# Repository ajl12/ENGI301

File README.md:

# Stress Buddy

The following repository contains files required to operate the Stress Buddy device created using a PocketBeagle.

For more information on how to build the device and connect hardware, visit: https://www.hackster.io/ajl12/stress-buddy-12f85d

# Initializing the PocketBeagle

To initialize the PocketBeagle, perform the following commands in the terminal:

1. sudo apt-get update
2. sudo apt-get install build-essential python-dev python-setuptools python-smbus -y
3. git clone https://github.com/adafruit/adafruit-beaglebone-io-python

# Code

To setup the code, pull the following repository from GitHub: https://github.com/ajl12/ENGI301

In the project_1 folder, 3 files are required to run the device. 

1. The configure_pins.sh file should be used by running the following command in the LINUX terminal:

	chmod 755 configure_pins.sh run

2. The project_1.py file contains the main code for running the device. 

3. The run file is needed to start the device. When ready to run the device, change directories  to var/lib/cloud9/ENGI301/project_1 and type the ./run command into the terminal. 

	Note: The run file also includes a python path to reference the ht16k33.py files under var/lib/cloud9/ENGI301/python

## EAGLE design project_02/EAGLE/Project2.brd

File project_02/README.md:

# Stress Buddy

The following repository contains EAGLE, Gerber, and documentation files required to create a PCB for the Stress Buddy device.

To learn more about the Stress Buddy device and obtain instructions for low-fidelity breadboard assembly, visit: https://www.hackster.io/ajl12/stress-buddy-12f85d

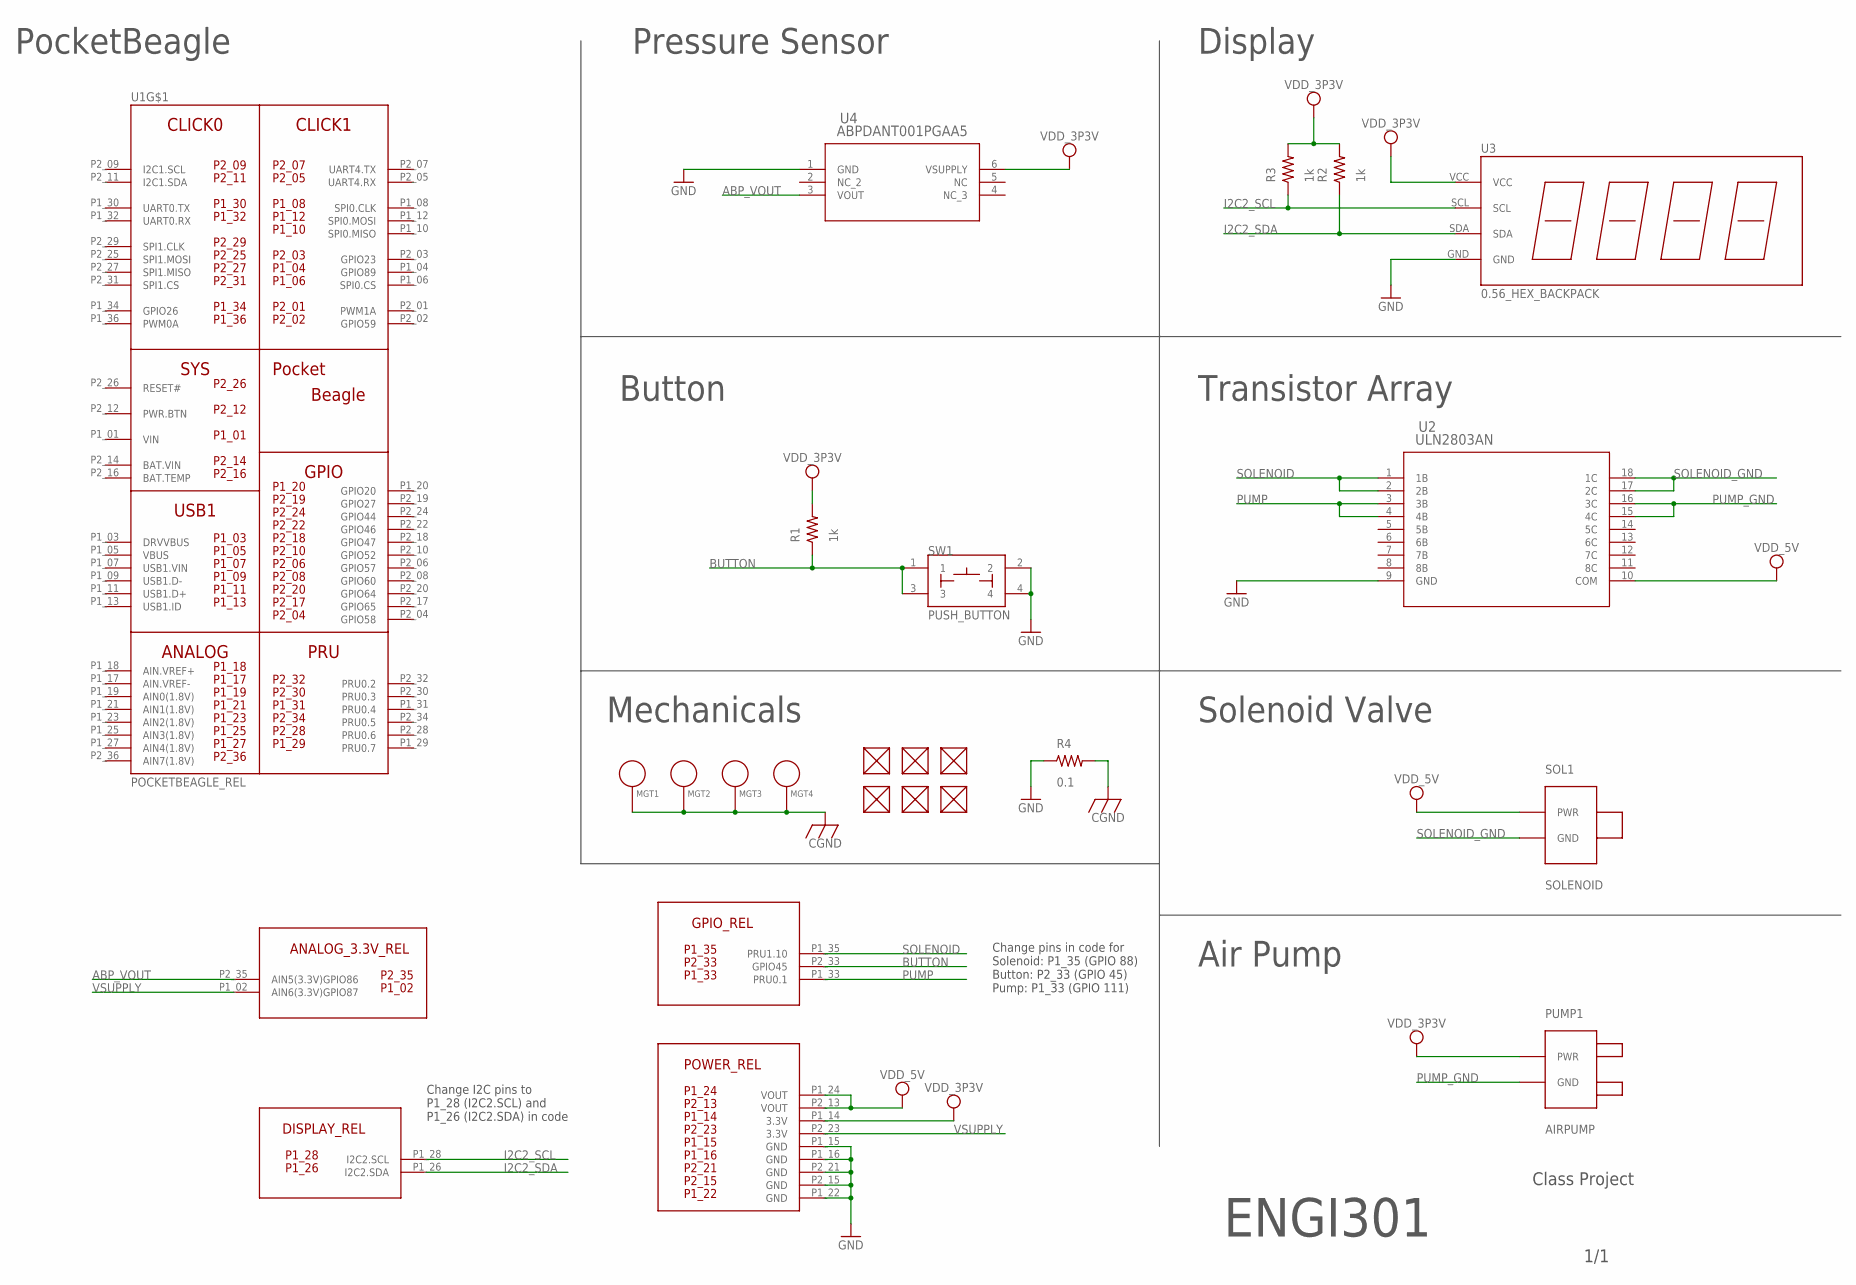
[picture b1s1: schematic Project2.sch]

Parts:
FUD1, FUD2, FUD3, FUD4, FUD5, FUD6: FIDUCIAL; FIDUCIAL_40MIL
MGT1, MGT2, MGT3, MGT4: MOUNTING_HOLE
PUMP1: AIRPUMP
R1, R2, R3: 1k; R0603
R4: 0.1; R0603
SOL1: SOLENOID
SW1: PUSH_BUTTON; BUTTON_12.5MM
U1: POCKETBEAGLE_REL; POCKETBEAGLE
U2: ULN2803AN; N18_TEX
U3: 0.56_HEX_BACKPACK
U4: ABPDANT001PGAA5; ABPDAN_HNW

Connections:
ABP_VOUT: U1.P2_35 (AIN5(3.3V)GPIO86), U4.3 (VOUT)
BAT.VIN: U1.P2_14 (BAT.VIN)
BUTTON: R1.1, SW1.1, SW1.3, U1.P2_33 (GPIO45)
CGND: MGT1.P$1, MGT2.P$1, MGT3.P$1, MGT4.P$1, R4.2
GND: R4.1, SW1.2, SW1.4, U1.P1_15 (GND), U1.P1_16 (GND), U1.P1_22 (GND), U1.P2_15 (GND), U1.P2_21 (GND), U2.9 (GND), U3.GND, U4.1 (GND)
I2C2_SCL: R3.1, U1.P1_28 (I2C2.SCL), U3.SCL
I2C2_SDA: R2.1, U1.P1_26 (I2C2.SDA), U3.SDA
PUMP: U1.P1_33 (PRU0.1), U2.3 (3B), U2.4 (4B)
PUMP_GND: PUMP1.GND1 (GND), U2.15 (4C), U2.16 (3C)
SOLENOID: U1.P1_35 (PRU1.10), U2.1 (1B), U2.2 (2B)
SOLENOID_GND: SOL1.GND, U2.17 (2C), U2.18 (1C)
VDD_3P3V: PUMP1.PWR1 (PWR), R1.2, R2.2, R3.2, U1.P1_14 (3.3V), U3.VCC, U4.6 (VSUPPLY)
VDD_5V: SOL1.PWR1 (PWR), U1.P1_24 (VOUT), U1.P2_13 (VOUT), U2.10 (COM)
VIN: U1.P1_01 (VIN)
VSUPPLY: U1.P1_02 (AIN6(3.3V)GPIO87), U1.P2_23 (3.3V)

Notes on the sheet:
PocketBeagle
Pressure Sensor
Button
Transistor Array
Display
Solenoid Valve
Air Pump
ENGI301
Class Project
1/1
Mechanicals
Change I2C pins to P1_28 (I2C2.SCL) and P1_26 (I2C2.SDA) in code
Change pins in code for Solenoid: P1_35 (GPIO 88) Button: P2_33 (GPIO 45) Pump: P1_33 (GPIO 111)

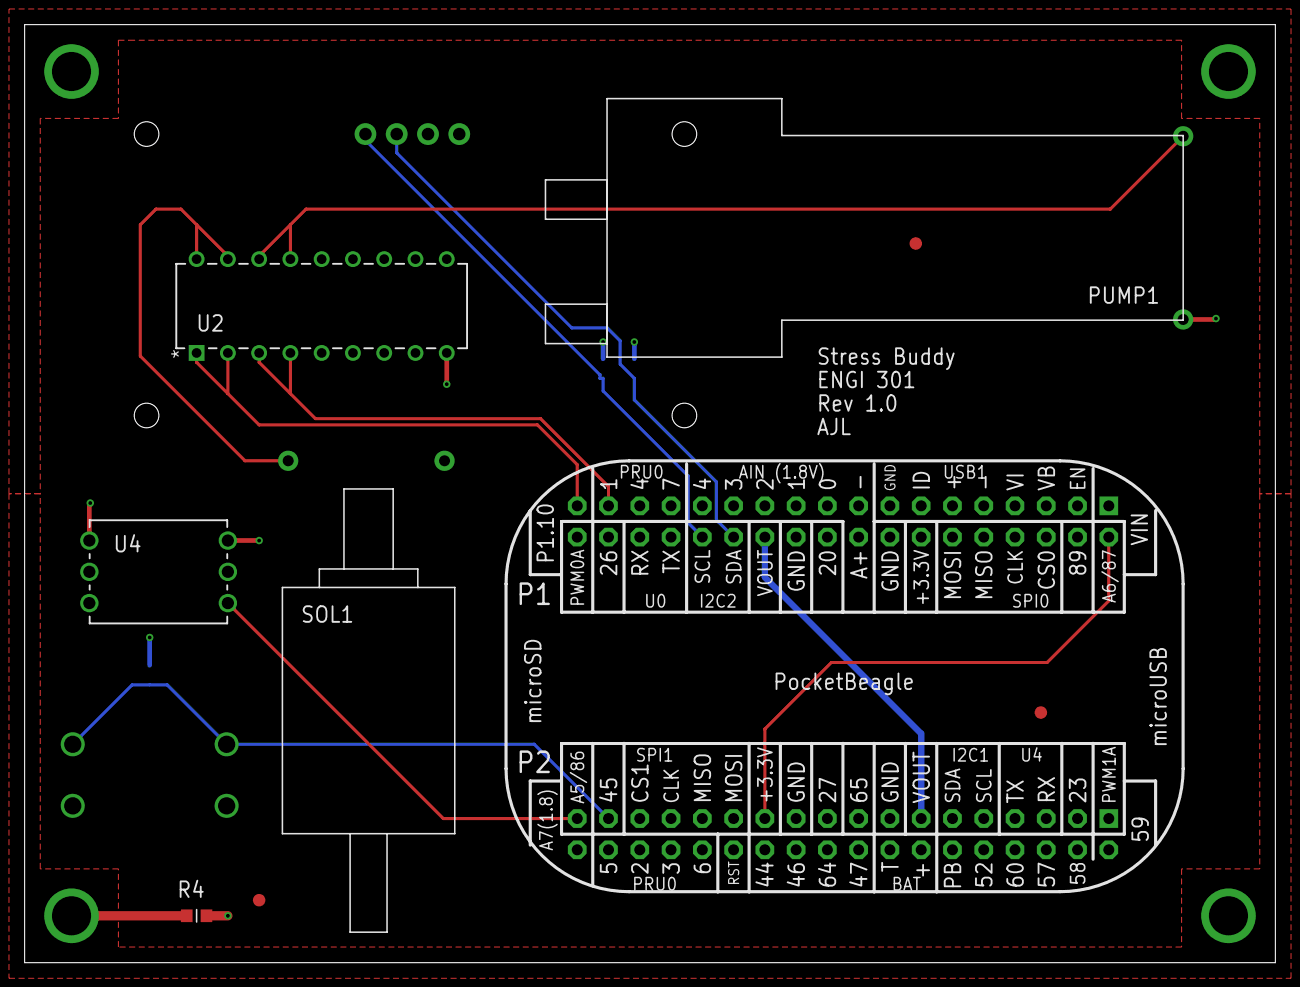
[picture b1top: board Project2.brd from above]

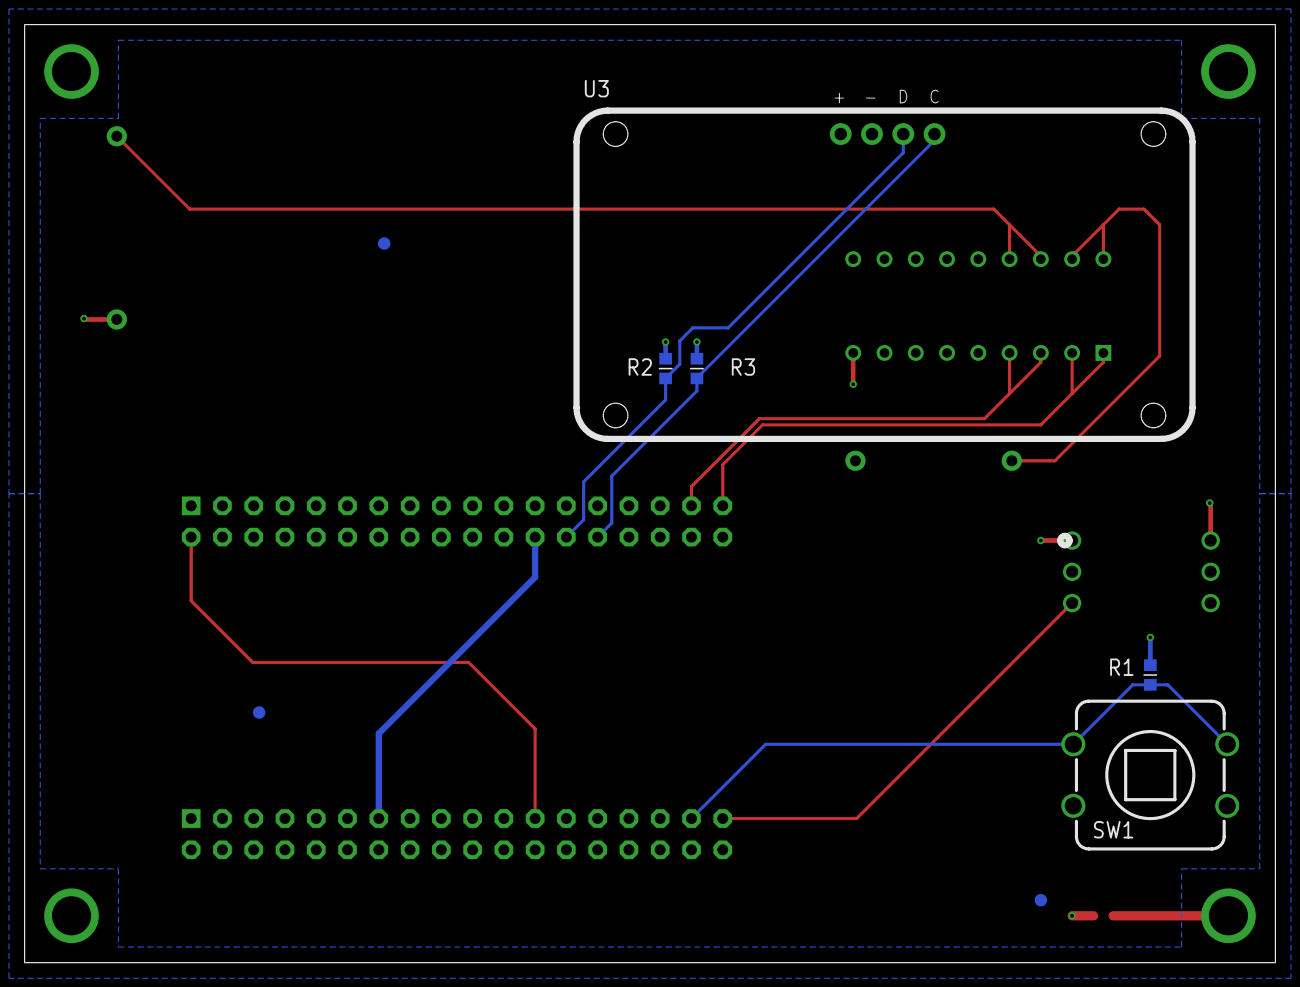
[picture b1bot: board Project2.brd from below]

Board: 4 copper layers, 101.6 x 76.2 mm, 21 parts (8 on the bottom side), 13 nets.

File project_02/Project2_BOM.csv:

"Qty";"Value";"Device";"Package";"Parts";"Description";"COPYRIGHT";"MANUFACTURER_PART_NUMBER";"MFR_NAME";
"1";"0.1";"R_R0603";"R0603";"R4";"RESISTOR, American symbol";"";"";"";
"1";"0.56_HEX_BACKPACK";"0.56_HEX_BACKPACK";"0.56_HEX_BACKPACK";"U3";"0.56" LED HEX Backback - Adafruit HT16K33 -";"";"";"";
"3";"1k";"R_R0603";"R0603";"R1, R2, R3";"RESISTOR, American symbol";"";"";"";
"1";"ABPDANT001PGAA5";"ABPDANT001PGAA5";"ABPDAN_HNW";"U4";"";"Copyright (C) 2021 Ultra Librarian. All rights reserved.";"ABPDANT005PGAA5";"Honeywell";
"1";"AIRPUMP";"AIRPUMP";"AIRPUMP";"PUMP1";"AIMELIAE 1PCS DC 3V Micro Vacuum Air Pump Mini Air Pressure Pump Medical Pump 30KPa 0.28L -";"";"";"";
"6";"FIDUCIAL";"FIDUCIAL";"FIDUCIAL_40MIL";"FUD1, FUD2, FUD3, FUD4, FUD5, FUD6";"";"";"";"";
"4";"MOUNTING_HOLE";"MOUNTING_HOLE";"MOUNTING_HOLE";"MGT1, MGT2, MGT3, MGT4";"Chassis Mounting Hole w/GND connection ability";"";"";"";
"1";"POCKETBEAGLE_REL";"POCKETBEAGLE_REL";"POCKETBEAGLE";"U1";"A PocketBeagle device with relevant components for the Stress Buddy project separated from the main schematic.";"";"";"";
"1";"PUSH_BUTTON";"PUSH_BUTTON";"BUTTON_12.5MM";"SW1";"";"";"";"";
"1";"SOLENOID";"SOLENOID";"SOLENOID";"SOL1";"Uxcell Miniature Solenoid Valve 2 Way Normally Closed DC4.5V 0.5A Air Solenoid Valve -";"";"";"";
"1";"ULN2803AN";"ULN2803AN";"N18_TEX";"U2";"";"Copyright (C) 2021 Ultra Librarian. All rights reserved.";"ULN2803AN";"Texas Instruments";

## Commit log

2021-09-15 Updating README.md
2021-10-05 Adding comments
2021-10-05 Homework 4 Submission
2021-10-07 Initial Submission 10/5
2021-10-07 Create test file
2021-10-07 Initial Submission 5/10
2021-10-15 Revised project proposal 10/14
2021-11-08 adding project files
2021-11-09 Final comments
2021-11-09 upload
2021-11-09 Updated with new block diagrams
2021-11-17 Create project_2

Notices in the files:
parts and their libraries:
COPYRIGHT: Copyright (C) 2021 Ultra Librarian. All rights reserved.
